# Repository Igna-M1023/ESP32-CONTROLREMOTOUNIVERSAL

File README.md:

# ESP32-CONTROLREMOTOUNIVERSAL
Control Remoto Universal con receptor y emisor IR, permite guardar codigos

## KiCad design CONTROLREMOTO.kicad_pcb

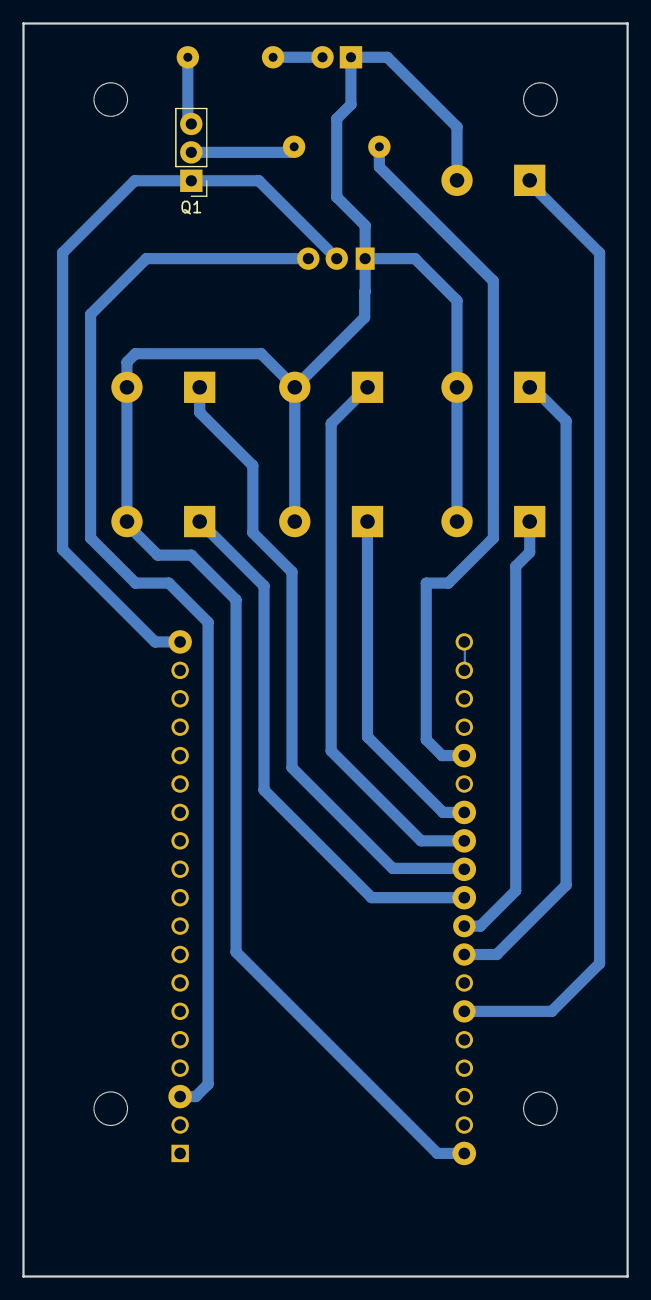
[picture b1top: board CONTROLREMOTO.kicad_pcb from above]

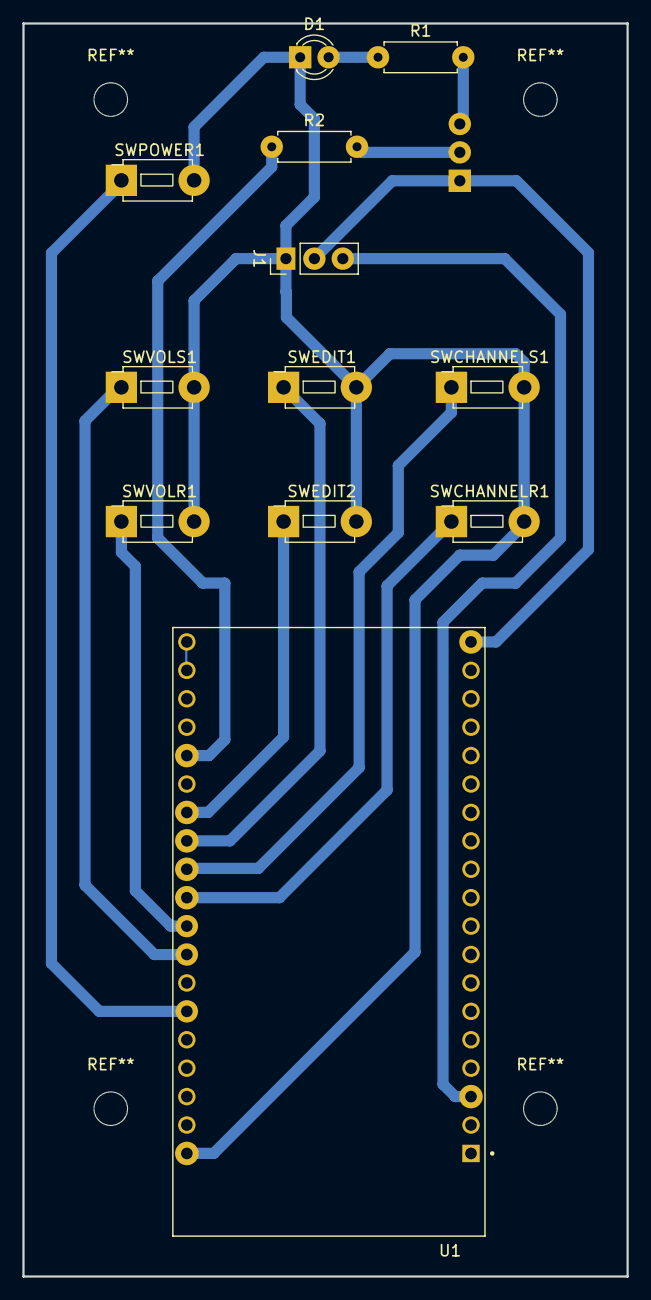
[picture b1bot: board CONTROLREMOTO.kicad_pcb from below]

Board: 2 copper layers, 54.0 x 112.0 mm, 13 parts (12 on the bottom side), 14 nets.

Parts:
D1: IR204A; LED_D3.0mm_IRBlack
J1: Conn_01x03_Socket; PinHeader_1x03_P2.54mm_Vertical
Q1: BC547; PinHeader_1x03_P2.54mm_Vertical
R1: 20; R_Axial_DIN0207_L6.3mm_D2.5mm_P7.62mm_Horizontal
R2: 330; R_Axial_DIN0207_L6.3mm_D2.5mm_P7.62mm_Horizontal
SWCHANNELR1: SW_Push; SW_PUSH_1P1T_6x3.5mm_H5.0_APEM_MJTP1250
SWCHANNELS1: SW_Push; SW_PUSH_1P1T_6x3.5mm_H5.0_APEM_MJTP1250
SWEDIT1, SWEDIT2: SW_Push; SW_PUSH_1P1T_6x3.5mm_H5.0_APEM_MJTP1250
SWPOWER1: SW_Push; SW_PUSH_1P1T_6x3.5mm_H5.0_APEM_MJTP1250
SWVOLR1: SW_Push; SW_PUSH_1P1T_6x3.5mm_H5.0_APEM_MJTP1250
SWVOLS1: SW_Push; SW_PUSH_1P1T_6x3.5mm_H5.0_APEM_MJTP1250
U1: ESP32-DEVKITC-32D; MODULE_ESP32-DEVKITC-32D

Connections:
GND: D1.1 (K), J1.1, SWCHANNELR1.2, SWCHANNELS1.2, SWEDIT1.2, SWEDIT2.2, SWPOWER1.2, SWVOLR1.2, SWVOLS1.2, U1.J3-1 (GND3)
unnamed: D1.2 (A), R1.1
unnamed: J1.2, Q1.1 (C), U1.J2-19 (EXT_5V)
unnamed: J1.3, U1.J2-3 (SENSOR_VP)
unnamed: Q1.2 (B), R2.2
unnamed: Q1.3 (E), R1.2
unnamed: R2.1, U1.J3-15 (IO2)
unnamed: SWEDIT2.1, U1.J3-13 (IO4)
unnamed: SWCHANNELR1.1, U1.J3-10 (IO5)
unnamed: SWEDIT1.1, U1.J3-12 (IO16)
unnamed: SWCHANNELS1.1, U1.J3-11 (IO17)
unnamed: SWVOLR1.1, U1.J3-9 (IO18)
unnamed: SWVOLS1.1, U1.J3-8 (IO19)
unnamed: SWPOWER1.1, U1.J3-6 (IO21)
